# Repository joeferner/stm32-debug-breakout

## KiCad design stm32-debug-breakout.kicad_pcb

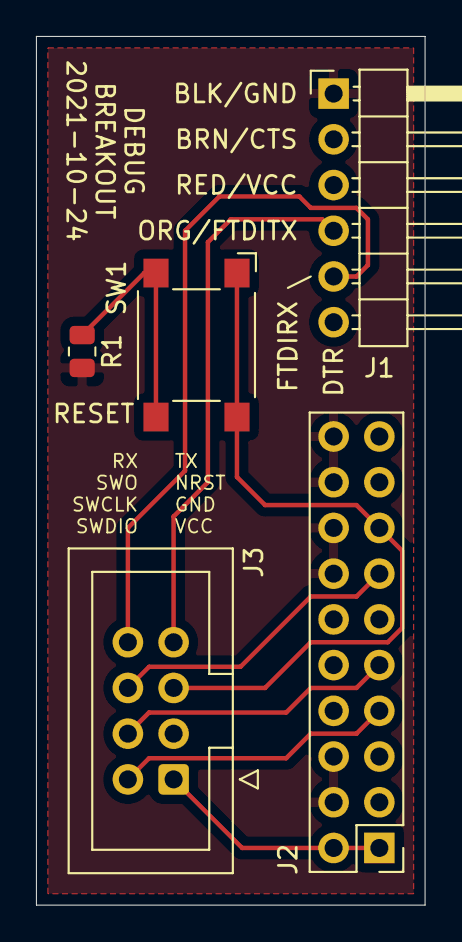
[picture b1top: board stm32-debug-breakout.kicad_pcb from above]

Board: 2 copper layers, 21.6 x 48.3 mm, 5 parts (0 on the bottom side), 9 nets.

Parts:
J1: FTDI; PinHeader_1x06_P2.54mm_Horizontal
J2: STLINK; PinHeader_2x10_P2.54mm_Vertical
J3: ST_PROGRAM_DEBUG; IDC-Header_2x04_P2.54mm_Vertical
R1: 0R; R_0805_2012Metric
SW1: SW_MEC_5E; SW_SPST_Omron_B3FS-100xP

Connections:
/NRST: J2.15, J3.5, SW1.1, SW1.2
/RX: J1.5, J3.8
/SWCLK: J2.9, J3.4
/SWDIO: J2.7, J3.2
/SWO: J2.13, J3.6
/TX: J1.4, J3.7
GND: J1.1, J2.4, J2.6, J2.8, J2.10, J2.12, J2.14, J2.16, J2.18, J2.20, J3.3, R1.2
unnamed: R1.1, SW1.3, SW1.4
VCC: J2.1, J2.2, J3.1

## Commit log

2021-10-24 initial
2021-10-24 2021-10-24
